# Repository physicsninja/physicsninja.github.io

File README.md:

This website is meant as an online repository of things I have written up that may or may not be useful to the world as well as to serve as a portfolio. The content that is my own (<em>i.e.</em> not the framework upon which this site is built, but rather the content that rests within it) is licensed under the [Creative Commons Attribution 4.0 license][1]. While not a condition of the license, it would be neat if you woul drop me a line at lambentmanifold@gmail.com so that I can know to what my work has led.

This website uses the [Feeling Responsive][1] theme constructed by Phlow and contributors.

[1]: http://phlow.github.io/feeling-responsive/documentation/

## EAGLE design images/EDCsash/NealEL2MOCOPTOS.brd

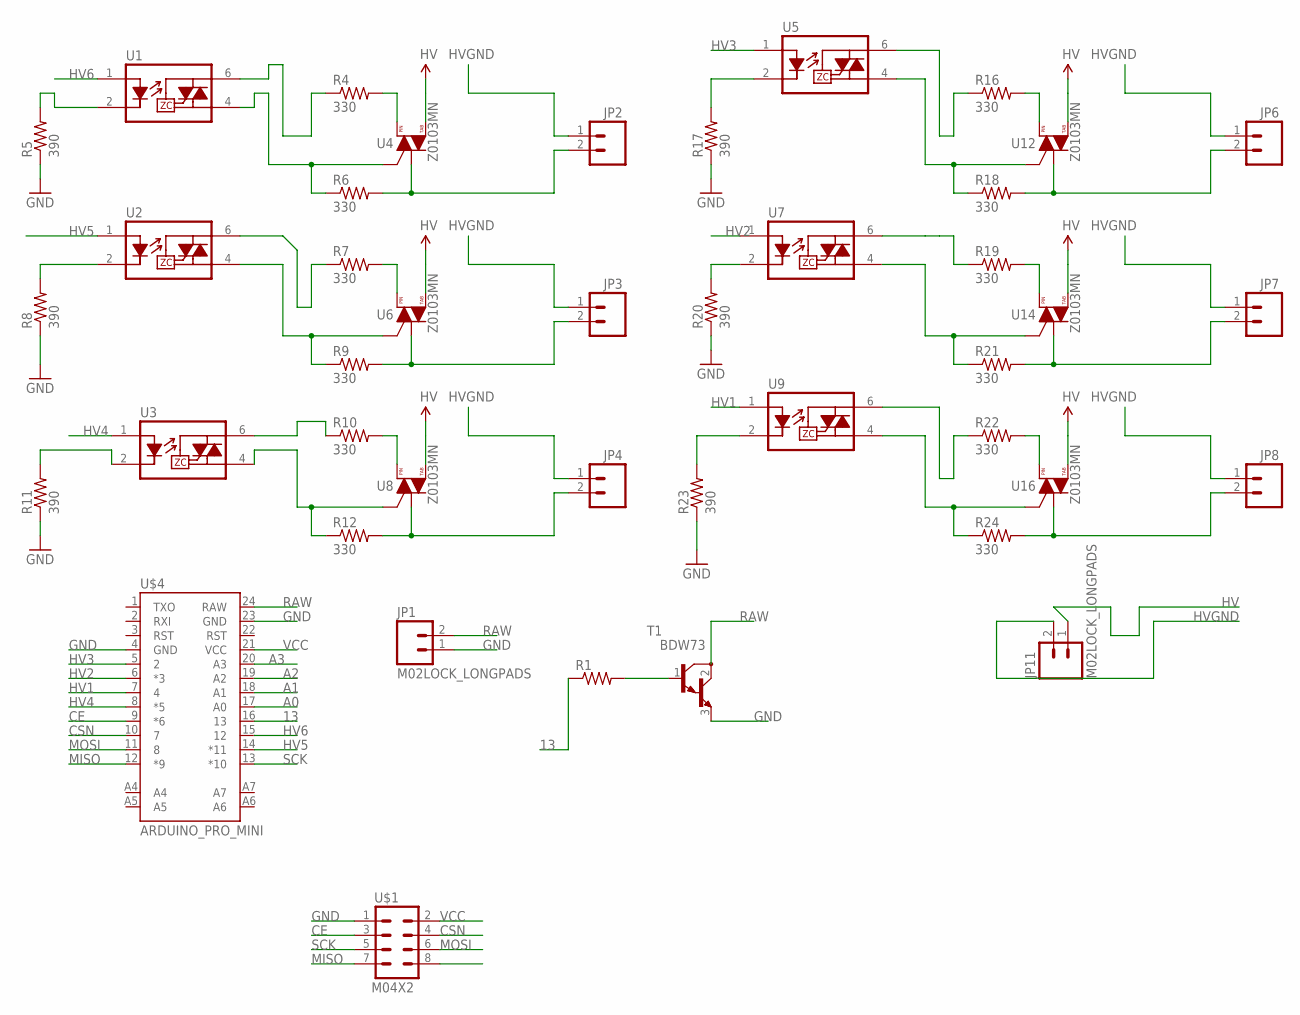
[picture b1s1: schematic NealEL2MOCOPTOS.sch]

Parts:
JP1, JP11: M02LOCK_LONGPADS; 1X02_LOCK_LONGPADS
JP2, JP3, JP4, JP6, JP7, JP8: M02PTH; 1X02
R1: RESISTORPTH-1/2W; AXIAL-0.5
R4, R6, R7, R9, R10, R12, R16, R18, R19, R21, R22, R24: 330; 0603-RES
R5, R8, R11, R17, R20, R23: 390; 0603-RES
T1: BDW73; TO220
U1, U2, U3, U5, U7, U9: MOC3063S; DIP8SMD
U4, U6, U8, U12, U14, U16: Z0103MN; SOT223
U$1: M04X2; 2X4
U$4: ARDUINO_PRO_MINI

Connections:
13: R1.P$1 (1), U$4.16 (13)
A0: U$4.17 (A0)
A1: U$4.18 (A1)
A2: U$4.19 (A2)
A3: U$4.20 (A3)
CE: U$1.3, U$4.9 (*6)
CSN: U$1.4, U$4.10 (7)
GND: JP1.1, R5.1, R8.1, R11.1, R17.1, R20.1, R23.1, T1.3 (E), U$1.1, U$4.4 (GND), U$4.23 (GND)
HV: JP11.1, U4.4 (T2), U6.4 (T2), U8.4 (T2), U12.4 (T2), U14.4 (T2), U16.4 (T2)
HV1: U9.1 (A), U$4.7 (4)
HV2: U7.1 (A), U$4.6 (*3)
HV3: U5.1 (A), U$4.5 (2)
HV4: U3.1 (A), U$4.8 (*5)
HV5: U2.1 (A), U$4.14 (*11)
HV6: U1.1 (A), U$4.15 (12)
HVGND: JP2.1, JP3.1, JP4.1, JP6.1, JP7.1, JP8.1, JP11.2
MISO: U$1.7, U$4.12 (*9)
MOSI: U$1.6, U$4.11 (8)
unnamed: R1.P$2 (2), T1.1 (B)
unnamed: R6.1, U1.4 (T2), U4.3 (G)
unnamed: R8.2, U2.2 (K)
unnamed: R4.1, U1.6 (T1)
unnamed: JP2.2, R6.2, U4.1 (T1)
unnamed: R10.1, U3.6 (T1)
unnamed: R9.1, U2.4 (T2), U6.3 (G)
unnamed: R7.1, U2.6 (T1)
unnamed: JP3.2, R9.2, U6.1 (T1)
unnamed: R5.2, U1.2 (K)
unnamed: R4.2, U4.2 (T2)
unnamed: R12.1, U3.4 (T2), U8.3 (G)
unnamed: JP4.2, R12.2, U8.1 (T1)
unnamed: R7.2, U6.2 (T2)
unnamed: R17.2, U5.2 (K)
unnamed: R20.2, U7.2 (K)
unnamed: R23.2, U9.2 (K)
unnamed: R10.2, U8.2 (T2)
unnamed: R18.1, U5.4 (T2), U12.3 (G)
unnamed: R16.1, U5.6 (T1)
unnamed: JP6.2, R18.2, U12.1 (T1)
unnamed: R21.1, U7.4 (T2), U14.3 (G)
unnamed: R19.1, U7.6 (T1)
unnamed: JP7.2, R21.2, U14.1 (T1)
unnamed: R16.2, U12.2 (T2)
unnamed: R24.1, U9.4 (T2), U16.3 (G)
unnamed: R22.1, U9.6 (T1)
unnamed: JP8.2, R24.2, U16.1 (T1)
unnamed: R19.2, U14.2 (T2)
unnamed: R22.2, U16.2 (T2)
unnamed: R11.2, U3.2 (K)
RAW: JP1.2, T1.2 (C), U$4.24 (RAW)
SCK: U$1.5, U$4.13 (*10)
VCC: U$1.2, U$4.21 (VCC)

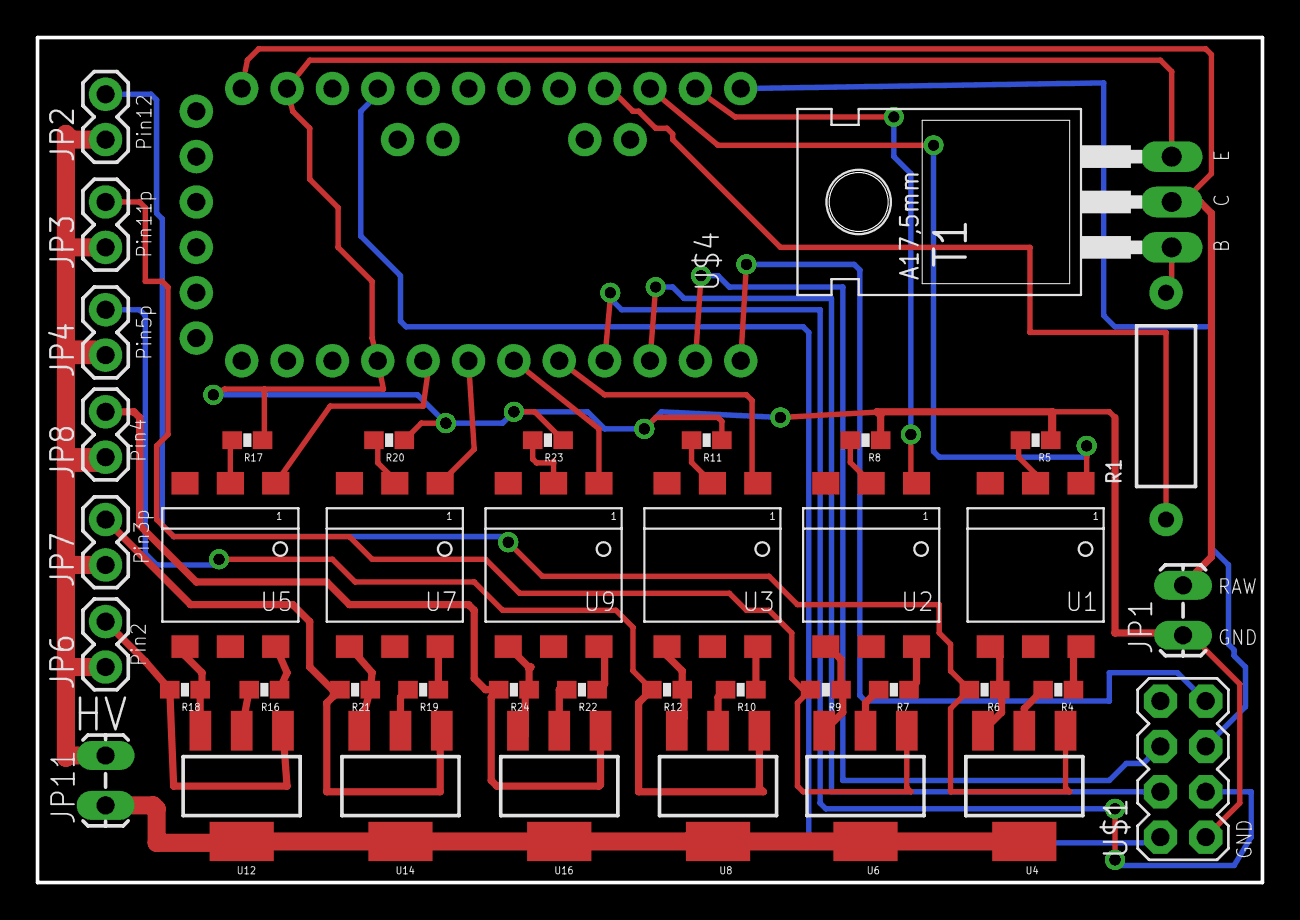
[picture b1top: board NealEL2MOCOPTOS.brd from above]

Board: 2 copper layers, 68.6 x 47.3 mm, 42 parts (0 on the bottom side), 48 nets.

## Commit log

2016-12-03 initial-ish commit
2016-12-20 updated to new theme
2016-12-20 Create CNAME
2017-01-03 Update CNAME
2017-01-23 initial public update
2017-01-23 directory fix
2017-01-23 directory fix2
2017-01-23 directory fix3
2017-01-23 old file clean up
2017-01-23 minor spelling fixes
2017-01-23 minor spelling fixes2
2017-01-23 updated contact
2017-01-23 updated contact2
2017-01-23 updated contact3
2017-01-23 revert
2017-01-23 image updates
2017-01-23 image updates2
2017-01-24 post edits
2017-01-24 social media edits
2017-01-24 category edits
2017-01-24 added a license statement
2017-01-24 widget image correction
2017-01-24 widget image correction3
2017-01-24 no with proper attribution
2017-01-24 grammar fixes
2017-01-24 copyright fixes
2017-05-23 =now with more pictures
2017-12-07 update bio
2017-12-07 update current source
2018-02-07 New post on STFMR
2018-02-07 fix broken link
2018-02-08 remove chaff
2018-02-08 remove fix labels
2018-02-08 minus sign fixes
2020-05-25 Bump ffi from 1.9.14 to 1.12.2
    Bumps [ffi](https://github.com/ffi/ffi) from 1.9.14 to 1.12.2.
    - [Release notes](https://github.com/ffi/ffi/releases)
    - [Changelog](https://github.com/ffi/ffi/blob/master/CHANGELOG.md)
    - [Commits](https://github.com/ffi/ffi/compare/1.9.14...1.12.2)
2020-05-25 Bump jekyll from 3.3.1 to 3.6.3
    Bumps [jekyll](https://github.com/jekyll/jekyll) from 3.3.1 to 3.6.3.
    - [Release notes](https://github.com/jekyll/jekyll/releases)
    - [Changelog](https://github.com/jekyll/jekyll/blob/master/History.markdown)
    - [Commits](https://github.com/jekyll/jekyll/compare/v3.3.1...v3.6.3)
2020-05-25 http->https
2020-05-26 updated bio
2020-05-26 new unicorn day post
2020-05-26 minor edits to unicorn day part2
2020-05-26 minor edits to unicorn day part2 link fixes
2020-05-26 typo fix
2020-05-26 typo fix2
2020-05-26 more photos
2020-05-26 more photos2
2020-05-26 switch to jpeg
2020-05-26 minor change to unicorns2
2020-08-08 Bump kramdown from 2.2.1 to 2.3.0
    Bumps [kramdown](https://github.com/gettalong/kramdown) from 2.2.1 to 2.3.0.
    - [Release notes](https://github.com/gettalong/kramdown/releases)
    - [Changelog](https://github.com/gettalong/kramdown/blob/master/doc/news.page)
    - [Commits](https://github.com/gettalong/kramdown/commits)
2021-03-29 Bump kramdown from 2.2.1 to 2.3.1
    Bumps [kramdown](https://github.com/gettalong/kramdown) from 2.2.1 to 2.3.1.
    - [Release notes](https://github.com/gettalong/kramdown/releases)
    - [Changelog](https://github.com/gettalong/kramdown/blob/master/doc/news.page)
    - [Commits](https://github.com/gettalong/kramdown/commits)
2021-04-30 Bump rexml from 3.2.4 to 3.2.5
    Bumps [rexml](https://github.com/ruby/rexml) from 3.2.4 to 3.2.5.
    - [Release notes](https://github.com/ruby/rexml/releases)
    - [Changelog](https://github.com/ruby/rexml/blob/master/NEWS.md)
    - [Commits](https://github.com/ruby/rexml/compare/v3.2.4...v3.2.5)
2021-07-12 Bump addressable from 2.7.0 to 2.8.0
    Bumps [addressable](https://github.com/sporkmonger/addressable) from 2.7.0 to 2.8.0.
    - [Release notes](https://github.com/sporkmonger/addressable/releases)
    - [Changelog](https://github.com/sporkmonger/addressable/blob/main/CHANGELOG.md)
    - [Commits](https://github.com/sporkmonger/addressable/compare/addressable-2.7.0...addressable-2.8.0)
    ---
    updated-dependencies:
2022-10-05 Bump addressable from 2.7.0 to 2.8.1
    Bumps [addressable](https://github.com/sporkmonger/addressable) from 2.7.0 to 2.8.1.
    - [Release notes](https://github.com/sporkmonger/addressable/releases)
    - [Changelog](https://github.com/sporkmonger/addressable/blob/main/CHANGELOG.md)
    - [Commits](https://github.com/sporkmonger/addressable/compare/addressable-2.7.0...addressable-2.8.1)
    ---
    updated-dependencies:

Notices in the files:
parts and their libraries:
SparkFun-Resistors: Licensing: Creative Commons ShareAlike 4.0 International - https://creativecommons.org/licenses/by-sa/4.0
